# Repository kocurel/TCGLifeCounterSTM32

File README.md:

# STATUS: **WIP**

## Project: [TCGLifeCounterSTM32]
> Based on the predecessor: **TCGLifeCounterESP32**

## Project Overview
An advanced life counter for Trading Card Games (TCG), serving as an evolution of the TCG Life Counter model. The main focus is on mechanical and electronic optimization, specifically targeting miniaturization (component height limit H < 3mm) and UI tactile improvements.

## Versioning
- **v0.0.5**: Power delivery changes, schematic cleanup, LCD pin labeling, switching to a 100-pin STM32
- **v0.0.4**: Minor fix
- **v0.0.3**: MCU power delivery circuit
- **v0.0.2**: Backlight power circuit
- **v0.0.1**: Initial Draft

## Hardware Architecture & Design Decisions

### 1. Power Management (Backlight)
LCD backlight power delivery is based on the **AP3012** step-up converter in a **Constant Current** configuration:
- **Current Stabilization**: Implemented Low-Side Sensing with an **82 Ohm** sense resistor, forcing a stable **15.24 mA** current for the LEDs.
- **Brightness Control**: Managed via the **SHDN** pin using a PWM signal.

### 2. UI & Mechanicals
- **Tactile Switches**: Switched to **Omron B3F-4050** (130gf) to reduce noise and improve actuation ergonomics.
- **Stack-up**: Maximum component height under the display is **1.5 mm**, ensuring a safe clearance margin within the 3 mm profile.

## Project Structure
- `/hardware` - KiCad 9.0 project files (Schematics, PCB, Libraries).
- `/docs` - Technical documentation and comparative analyses:
    - `backlight_analysis.txt` - Detailed analysis of the FB loop and capacitor selection.
    - `switch_analysis.txt` - Comparison of switch acoustic parameters.
- `/firmware` - MCU source code (C/C++).

## Getting Started
### Prerequisites
- **KiCad 9.0+** (Required to open the latest `.kicad_pro` files).

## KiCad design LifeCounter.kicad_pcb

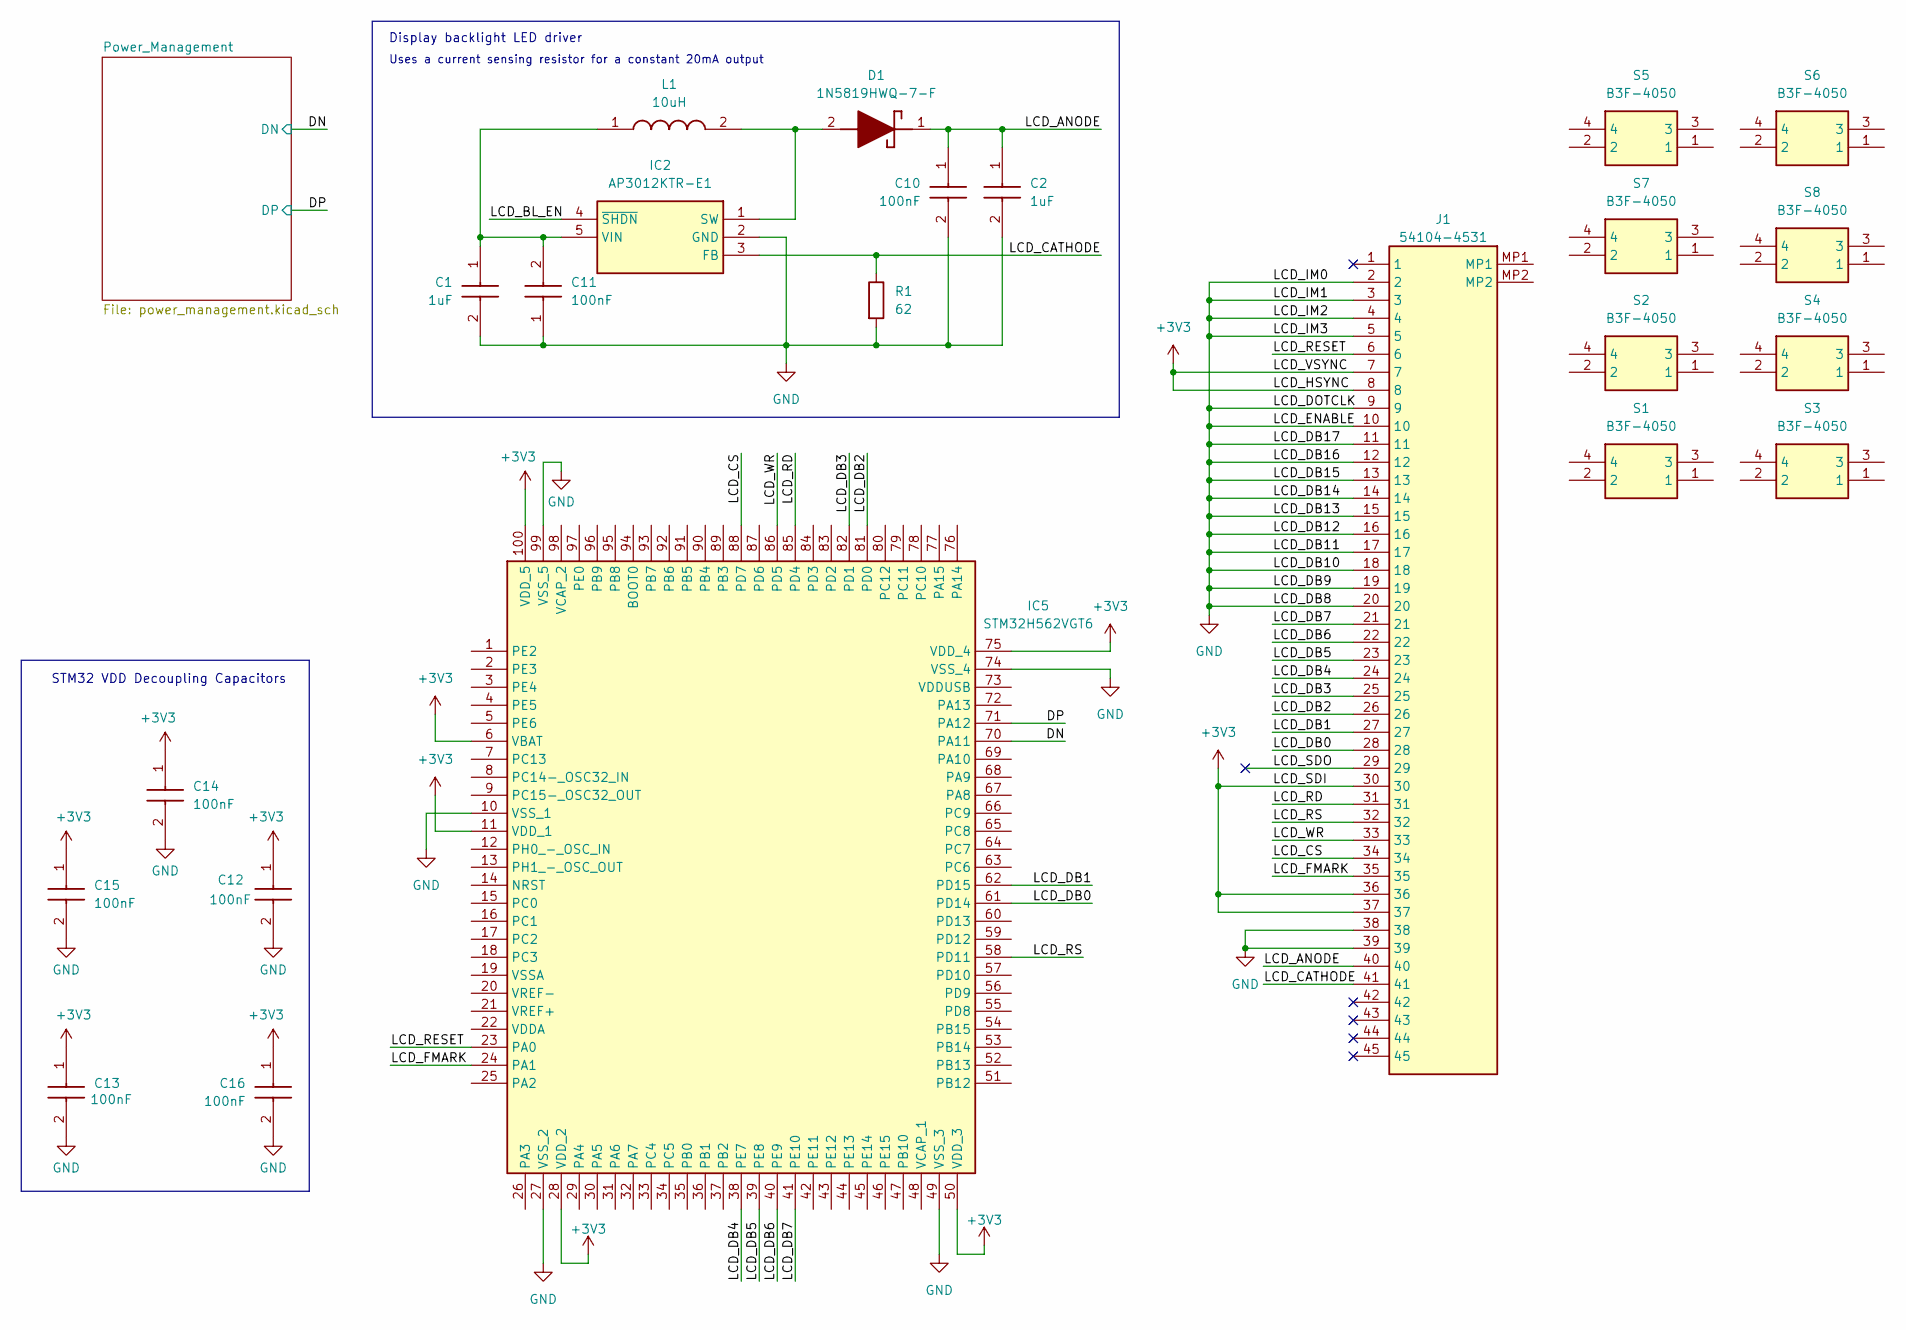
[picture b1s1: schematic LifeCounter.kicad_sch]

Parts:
C1: 1uF; Samsung_CAPC1608X90M; Manufacturer_Part_Number CL10B105KO8NNNC
C2: 1uF; Samsung_CAPC2012X135M; Manufacturer_Part_Number CL21B105KBFNNNE
C10: 100nF; Samsung_CAPC1608X90M; Manufacturer_Part_Number CL10B104KB8NNNC
C11, C12, C13, C14, C15, C16: 100nF; Kyocera_CAPC1608X90M; Manufacturer_Part_Number 06033D104KAT2A
D1: 1N5819HWQ-7-F; Diodes-Inc_SOD3716X145M; Manufacturer_Part_Number 1N5819HWQ-7-F
IC2: AP3012KTR-E1; Diodes-Inc_SOT95P282X145-5M; Manufacturer_Part_Number AP3012KTR-E1
IC5: STM32H562VGT6; STMicroelectronics_QFP50P1600X1600X160-100M; Manufacturer_Part_Number STM32H562VGT6
J1: 54104-4531; Molex_54104-4531; Mouser Part Number 538-54104-4531
L1: 10uH; TDK_VLS3012; Manufacturer_Part_Number VLS3012CX-100M-1
R1: 62; R_0805_2012Metric_Pad1.20x1.40mm_HandSolder
S1, S2, S3, S4, S5, S6, S7, S8: B3F-4050; Omron_B3F4050; Manufacturer_Part_Number B3F-4050

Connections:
+3V3: C12.1, C13.1, C14.1, C15.1, C16.1, IC5.6 (VBAT), IC5.11 (VDD_1), IC5.28 (VDD_2), IC5.50 (VDD_3), IC5.75 (VDD_4), IC5.100 (VDD_5), J1.7, J1.8, J1.30, J1.36, J1.37; also elsewhere on the board
/DN: IC5.70 (PA11); also elsewhere on the board
/DP: IC5.71 (PA12); also elsewhere on the board
/LCD_ANODE: C2.1, C10.1, D1.1 (K), J1.40
/LCD_BL_EN: IC2.4 (~SHDN)
/LCD_CATHODE: IC2.3 (FB), J1.41, R1.1
/LCD_CS: IC5.88 (PD7), J1.34
/LCD_DB0: IC5.61 (PD14), J1.28
/LCD_DB1: IC5.62 (PD15), J1.27
/LCD_DB2: IC5.81 (PD0), J1.26
/LCD_DB3: IC5.82 (PD1), J1.25
/LCD_DB4: IC5.38 (PE7), J1.24
/LCD_DB5: IC5.39 (PE8), J1.23
/LCD_DB6: IC5.40 (PE9), J1.22
/LCD_DB7: IC5.41 (PE10), J1.21
/LCD_FMARK: IC5.24 (PA1), J1.35
/LCD_RD: IC5.85 (PD4), J1.31
/LCD_RESET: IC5.23 (PA0), J1.6
/LCD_RS: IC5.58 (PD11), J1.32
/LCD_SDO: J1.29
/LCD_WR: IC5.86 (PD5), J1.33
GND: C1.2, C2.2, C10.2, C11.1, C12.2, C13.2, C14.2, C15.2, C16.2, IC2.2 (GND), IC5.10 (VSS_1), IC5.27 (VSS_2), IC5.49 (VSS_3), IC5.74 (VSS_4), IC5.99 (VSS_5), J1.2, J1.3, J1.4, J1.5, J1.9, J1.10, J1.11, J1.12, J1.13, J1.14, J1.15, J1.16, J1.17, J1.18, J1.19, J1.20, J1.38, J1.39, R1.2; also elsewhere on the board
unnamed: D1.2 (A), IC2.1 (SW), L1.2
unnamed: C1.1, C11.2, IC2.5 (VIN), L1.1

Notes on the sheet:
STM32 VDD Decoupling Capacitors
Uses a current sensing resistor for a constant 20mA output
Display backlight LED driver

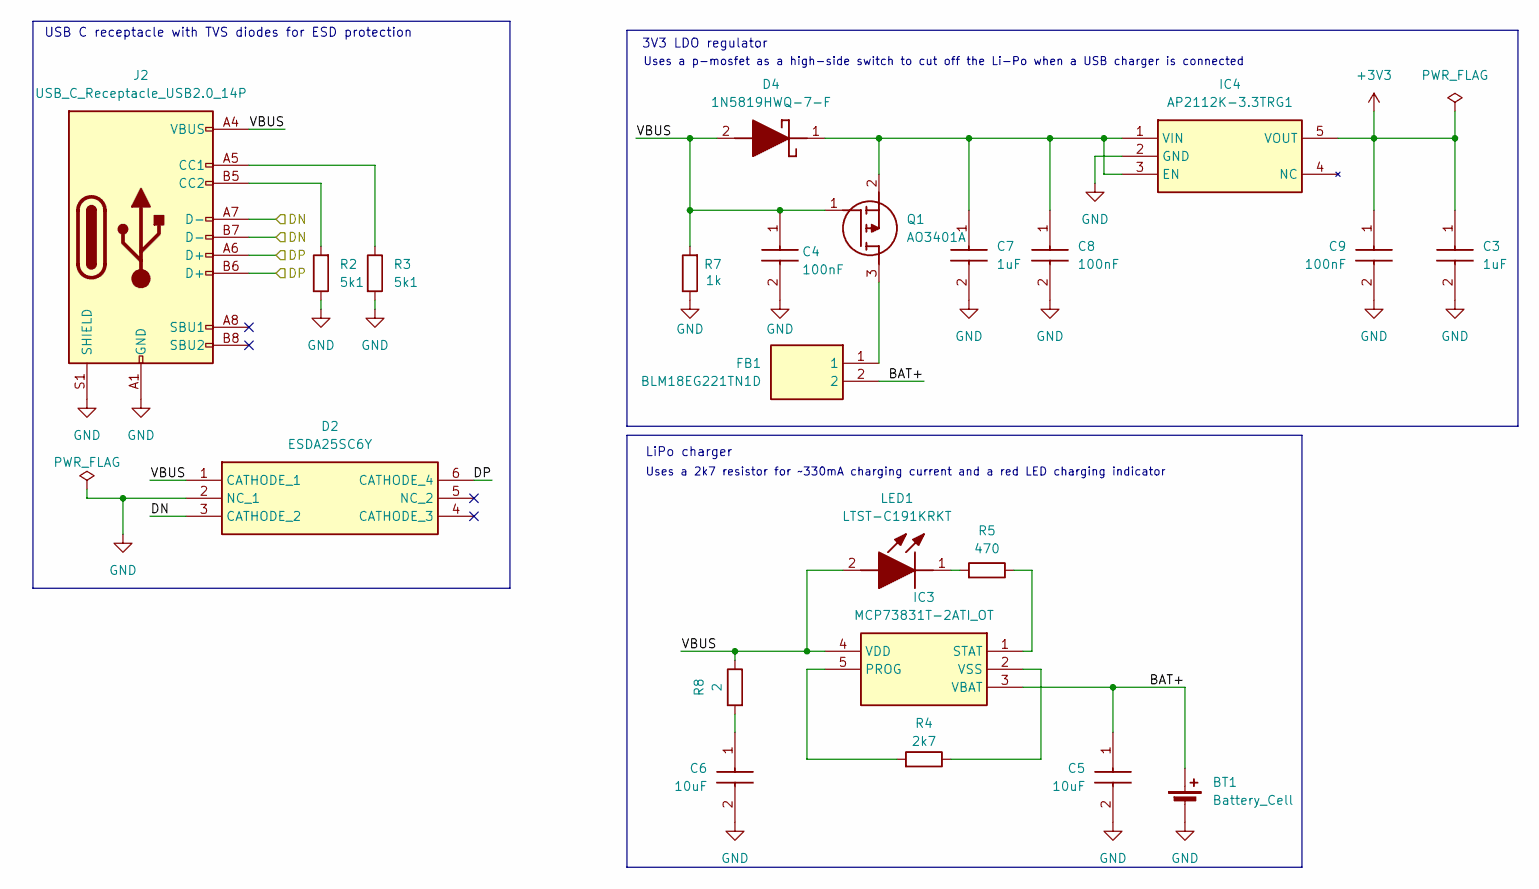
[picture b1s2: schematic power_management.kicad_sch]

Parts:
BT1: Battery_Cell
C3, C7: 1uF; Samsung_CAPC1608X90M; Manufacturer_Part_Number CL10B105KO8NNNC
C4, C8, C9: 100nF; Kemet_C0603; Manufacturer_Part_Number C0603C104K8RACTU
C5, C6: 10uF; Murata_GRM18x; Manufacturer_Part_Number GRM188R61E106KA73D
D2: ESDA25SC6Y; STMicroelectronics_SOT95P280X145-6M; Manufacturer_Part_Number ESDA25SC6Y
D4: 1N5819HWQ-7-F; Diodes-Inc_SOD3716X145M; Manufacturer_Part_Number 1N5819HWQ-7-F
FB1: BLM18EG221TN1D; Murata_BLM18EG101TH1D; Manufacturer_Part_Number BLM18EG221TN1D
IC3: MCP73831T-2ATI_OT; Microchip_SOT95P270X145-5M; Manufacturer_Part_Number MCP73831T-2ATI/OT
IC4: AP2112K-3.3TRG1; Diodes_Inc-SOT95P285X140-5M; Manufacturer_Part_Number AP2112K-3.3TRG1
J2: USB_C_Receptacle_USB2.0_14P; USB_C_Receptacle_GCT_USB4105-xx-A_16P_TopMnt_Horizontal
LED1: LTST-C191KRKT; Liteon_LEDC1608X55M; Manufacturer_Part_Number LTST-C191KRKT
Q1: AO3401A; Alpha&Omega_SOT95P280X125-3M; Manufacturer_Part_Number AO3401A
R2, R3: 5k1; R_0603_1608Metric_Pad0.98x0.95mm_HandSolder
R4: 2k7; R_0603_1608Metric_Pad0.98x0.95mm_HandSolder
R5: 470; R_0603_1608Metric_Pad0.98x0.95mm_HandSolder
R7: 1k; R_0603_1608Metric_Pad0.98x0.95mm_HandSolder
R8: 2; R_0603_1608Metric_Pad0.98x0.95mm_HandSolder

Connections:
+3V3: C3.1, C9.1, IC4.5 (VOUT); also elsewhere on the board
/DN: D2.3 (CATHODE_2), J2.A7 (D-), J2.B7 (D-); also elsewhere on the board
/DP: D2.6 (CATHODE_4), J2.A6 (D+), J2.B6 (D+); also elsewhere on the board
/Power_Management/BAT+: BT1.1 (+), C5.1, FB1.2, IC3.3 (VBAT)
/Power_Management/VBUS: C4.1, D2.1 (CATHODE_1), D4.2 (A), IC3.4 (VDD), J2.A4 (VBUS), J2.A9 (VBUS), J2.B4 (VBUS), J2.B9 (VBUS), LED1.2 (A), Q1.1 (G), R7.2, R8.1
GND: BT1.2 (-), C3.2, C4.2, C5.2, C6.2, C7.2, C8.2, C9.2, D2.2 (NC_1), IC4.2 (GND), J2.A1 (GND), J2.A12 (GND), J2.B1 (GND), J2.B12 (GND), J2.S1 (SHIELD), R2.1, R3.2, R7.1; also elsewhere on the board
unnamed: C6.1, R8.2
unnamed: C7.1, C8.1, D4.1 (K), IC4.1 (VIN), IC4.3 (EN), Q1.2 (S)
unnamed: IC3.5 (PROG), R4.2
unnamed: IC3.1 (STAT), R5.1
unnamed: IC3.2 (VSS), R4.1
unnamed: J2.A5 (CC1), R3.1
unnamed: J2.B5 (CC2), R2.2
unnamed: LED1.1 (K), R5.2
unnamed: FB1.1, Q1.3 (D)

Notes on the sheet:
Uses a 2k7 resistor for ~330mA charging current and a red LED charging indicator
3V3 LDO regulator
USB C receptacle with TVS diodes for ESD protection
Uses a p-mosfet as a high-side switch to cut off the Li-Po when a USB charger is connected
LiPo charger

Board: 4 copper layers, 44 parts (21 on the bottom side), 33 nets, no tracks yet.

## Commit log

2026-02-07 initial create
2026-02-07 added .gitignore
2026-02-07 renamed project and removed old files
2026-02-07 modified gitignore to ingore the backups
2026-02-07 fixed backups again
2026-02-07 renamed project again
2026-02-07 added tact switch
2026-02-07 added step-uop converter and inductor for backlight's LED power
2026-02-07 imported the new footprints to footprints library
2026-02-07 added schottky, step-up converter and inductor
2026-02-07 finished the power circuit for the LCD backlight
2026-02-08 bump version to v0.0.3, add USB C and TVS diode
2026-02-08 added a 10uF 0603 capacitor for usb c VBUS
2026-02-08 added lipo charger and red led indicator diode
2026-02-08 added 4.7uF capacitors for the lipo charger
2026-02-08 added LDO for 3v3 power delivery and a 100nF capacitor
2026-02-08 bump version to v0.0.4
2026-02-08 FIX: added missing GND on lcd backlight driver
2026-02-09 capacitor changes
2026-02-09 divided schematic into two sheets
2026-02-09 cleaned up and annotated the schematic
2026-02-09 modified the LDO circuit by adding a p-mosfet high side switch
2026-02-09 labeled the FPC tape connector (LCD) pins
2026-02-09 labeled the LCD pins and switched over to a 100 pin stm32 package
2026-02-09 fix: added a 2ohm resistor to prevent voltage spikes on USB-C input (LC)
2026-02-10 bump version to v0.0.5
2026-02-10 fixed: changedthe orientation of the AO3401A mosfet
2026-02-10 added a ferride bead, added a 100nF filtering cap to the mosfet gate and changed the resistor pulldown value from 100k to 1k, removed the 1k resistor in series at the gate pin
2026-04-17 Revise project name and predecessor in README
    Updated project name and predecessor references in README.
2026-04-17 Revise power management and UI details in README
    Updated power management and UI sections in README.
2026-04-17 Update brightness control description in README
    Removed frequency recommendation for PWM signal in brightness control section.
2026-04-23 Revise power management details in README
    Updated hardware architecture section with power management details.
2026-04-23 Update README with WIP status and project overview
    Added WIP status to the README
2026-04-23 Fix formatting of STATUS heading in README
2026-05-17 Revise README for project overview and versioning
    Updated project description and versioning details in README.
2026-05-17 Update README to remove project details
    Removed project overview and versioning details from README.
2026-05-17 Remove duplicated line
